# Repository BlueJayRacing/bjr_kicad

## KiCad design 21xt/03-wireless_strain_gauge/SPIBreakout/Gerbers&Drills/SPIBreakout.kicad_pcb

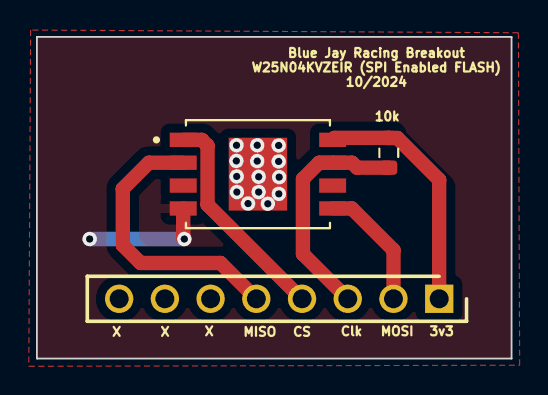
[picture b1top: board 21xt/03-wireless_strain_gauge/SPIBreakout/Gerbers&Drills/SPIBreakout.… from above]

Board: 2 copper layers, 26.4 x 17.9 mm, 3 parts (0 on the bottom side), 5 nets.

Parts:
10k: Rpu; R_0603_1608Metric
F1: SPIFLASH
J1: 61300811821; RHDR8W60P0X254_1X8_2082X250X850P

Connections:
CS: F1.1 (CS#), J1.4
Clk: 10k.2, F1.7 (CLK), J1.3
D0/MISO: F1.2 (DO(IO1)), J1.5
DI/MOSI: F1.5 (DI(IO0)), J1.2
VCC: 10k.1, F1.8 (VCC), J1.1

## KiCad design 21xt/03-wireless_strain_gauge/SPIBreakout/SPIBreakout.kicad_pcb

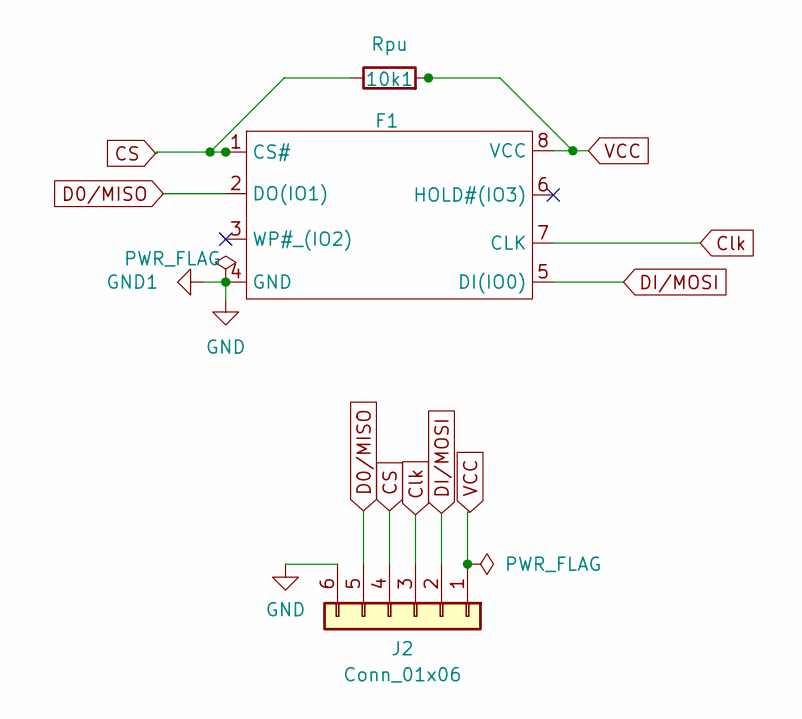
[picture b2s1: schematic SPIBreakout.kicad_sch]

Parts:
10k1: Rpu; R_0603_1608Metric
F1: SPIFLASH
J2: Conn_01x06; PinHeader_1x06_P2.00mm_Vertical

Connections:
CS: 10k1.1, F1.1 (CS#), J2.4
Clk: F1.7 (CLK), J2.3
D0/MISO: F1.2 (DO(IO1)), J2.5
DI/MOSI: F1.5 (DI(IO0)), J2.2
GND: F1.4 (GND), J2.6
VCC: 10k1.2, F1.8 (VCC), J2.1

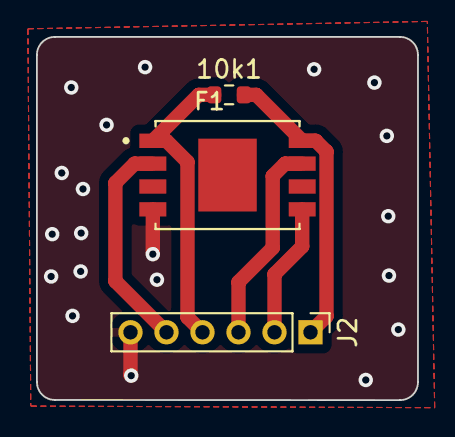
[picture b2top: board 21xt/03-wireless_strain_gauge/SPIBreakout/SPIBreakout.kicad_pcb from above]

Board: 2 copper layers, 21.2 x 20.2 mm, 3 parts (0 on the bottom side), 6 nets.

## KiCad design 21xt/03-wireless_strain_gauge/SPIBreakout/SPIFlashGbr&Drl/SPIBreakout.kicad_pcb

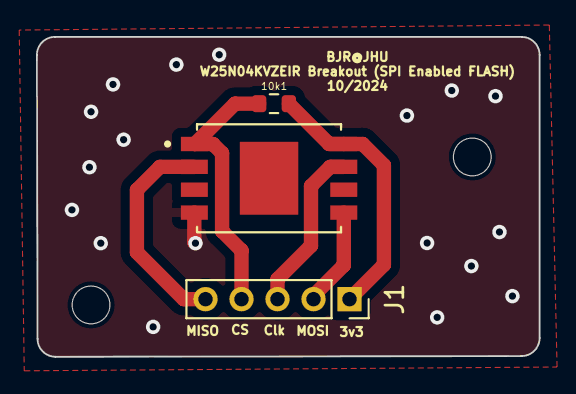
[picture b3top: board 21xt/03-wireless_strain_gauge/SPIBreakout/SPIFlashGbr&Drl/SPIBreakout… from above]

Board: 2 copper layers, 27.9 x 17.8 mm, 3 parts (0 on the bottom side), 5 nets.

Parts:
10k1: Rpu; R_0603_1608Metric
F1: SPIFLASH
J1: Conn_01x05; PinSocket_1x05_P2.00mm_Vertical

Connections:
CS: 10k1.1, F1.1 (CS#), J1.4
Clk: F1.7 (CLK), J1.3
D0/MISO: F1.2 (DO(IO1)), J1.5
DI/MOSI: F1.5 (DI(IO0)), J1.2
VCC: 10k1.2, F1.8 (VCC), J1.1

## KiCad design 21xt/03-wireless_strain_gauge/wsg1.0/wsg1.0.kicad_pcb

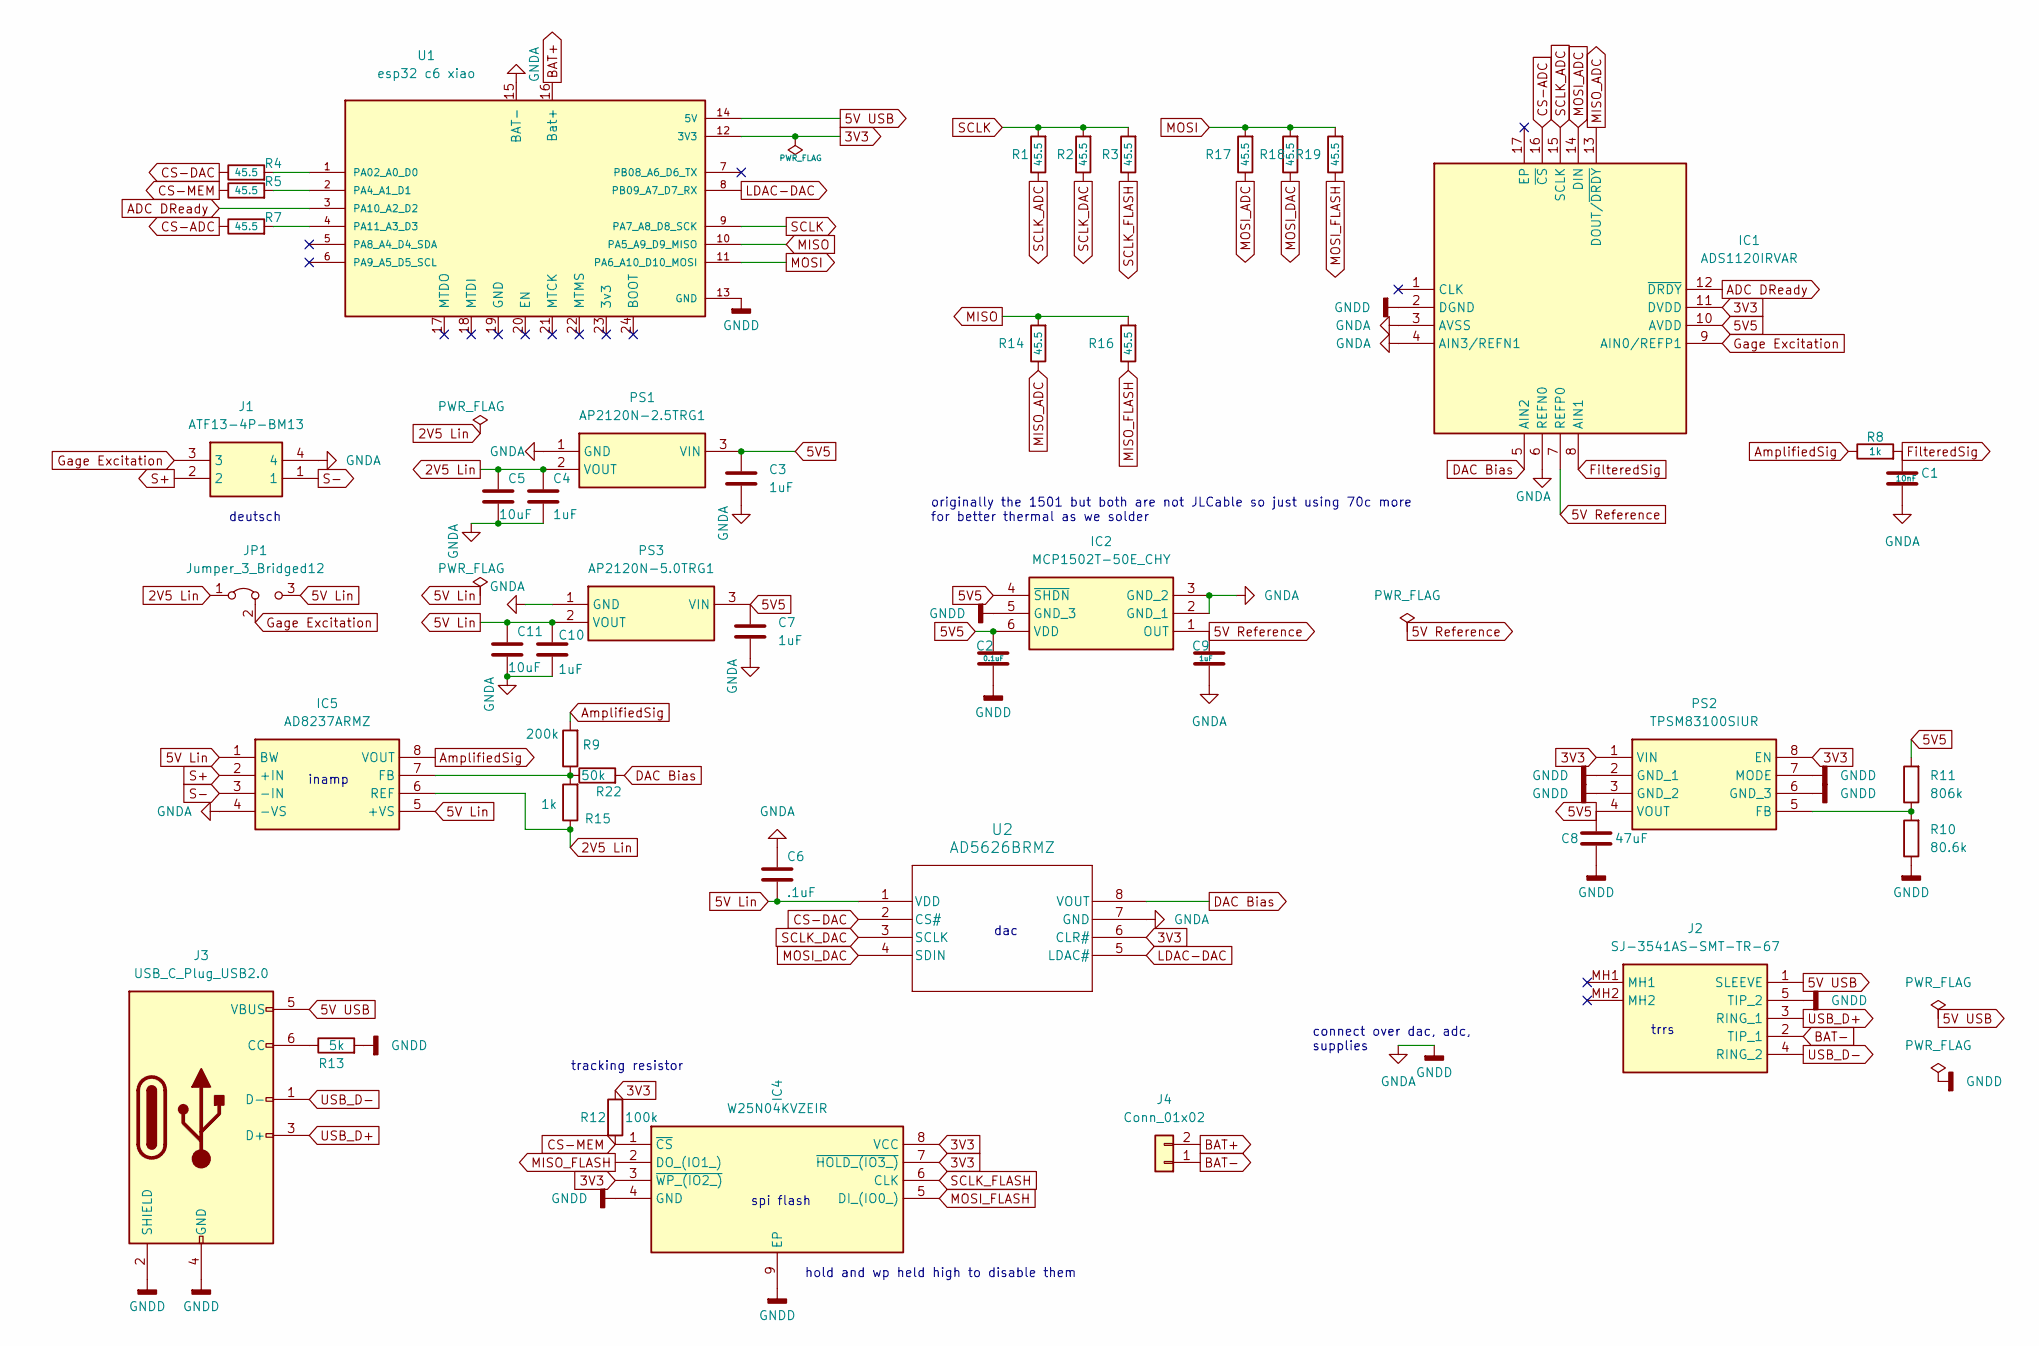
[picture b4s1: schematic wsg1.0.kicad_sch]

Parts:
C1: 10nF; C_0402_1005Metric
C2: 0.1uF; C_0402_1005Metric
C3, C4, C7, C9, C10: 1uF; C_0402_1005Metric
C5, C11: 10uF; C_0402_1005Metric
C6: .1uF; C_0402_1005Metric
C8: 47uF; C_0805_2012Metric
IC1: ADS1120IRVAR; QFN50P350X350X100-17N-D; Mouser Part Number 595-ADS1120IRVAR
IC2: MCP1502T-50E_CHY; SOT95P280X145-6N; Mouser Part Number 579-MCP1501T-50E/CHY
IC4: W25N04KVZEIR; SON127P800X600X80-9N-D; Mouser Part Number 454-W25N04KVZEIR
IC5: AD8237ARMZ; SOP65P490X110-8N; Mouser Part Number 584-AD8237ARMZ
J1: ATF13-4P-BM13; DTF134PG003; Mouser Part Number 571-DTF13-4P-G003
J2: SJ-3541AS-SMT-TR-67; SJ3541ASSMTTR67; Manufacturer_Part_Number SJ-3541AS-SMT-TR-67
J3: USB_C_Plug_USB2.0; USB_C_PLACE
J4: Conn_01x02; JST_PH_S2B-PH-K_1x02_P2.00mm_Horizontal
JP1: Jumper_3_Bridged12; SolderJumper-3_P2.0mm_Open_TrianglePad1.0x1.5mm
PS1: AP2120N-2.5TRG1; Mouser Part Number 621-AP2120N-5.0TRG1
PS2: TPSM83100SIUR; Mouser Part Number 595-TPSM83100SIUR
PS3: AP2120N-5.0TRG1; Mouser Part Number 621-AP2120N-5.0TRG1
R1, R2, R3, R4, R5, R7, R14, R16, R17, R18, R19: 45.5; R_0402_1005Metric
R8, R15: 1k; R_0402_1005Metric
R9: 200k; R_0402_1005Metric
R10: 80.6k; R_0402_1005Metric
R11: 806k; R_0402_1005Metric
R12: 100k; R_0402_1005Metric
R13: 5k; R_0402_1005Metric
R22: 50k; R_0402_1005Metric
U1: esp32 c6 xiao; esp32 c6 smt; PARTREV N/A
U2: AD5626BRMZ; AD5626

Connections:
2V5 Lin: C4.1, C5.1, IC5.6 (REF), JP1.1 (A), PS1.2 (VOUT), R15.1
3V3: IC1.11 (DVDD), IC4.3 (~WP_(IO2_)), IC4.7 (~HOLD_(IO3_)), IC4.8 (VCC), PS2.1 (VIN), PS2.8 (EN), R12.1, U1.12 (3V3), U2.6 (CLR#)
5V5: C2.1, C3.1, C7.1, C8.1, IC1.10 (AVDD), IC2.4 (~SHDN), IC2.6 (VDD), PS1.3 (VIN), PS2.4 (VOUT), PS3.3 (VIN), R11.2
5V Lin: C6.2, C10.1, C11.1, IC5.1 (BW), IC5.5 (+VS), JP1.3 (B), PS3.2 (VOUT), U2.1 (VDD)
5V Reference: C9.1, IC1.7 (REFP0), IC2.1 (OUT)
5V USB: J2.1 (SLEEVE), J3.5 (VBUS), U1.14 (5V)
ADC DReady: IC1.12 (~DRDY), U1.3 (PA10_A2_D2)
AmplifiedSig: IC5.8 (VOUT), R8.1, R9.2
BAT+: J4.2, U1.16 (Bat+)
BAT-: J2.2 (TIP_1), J4.1
CS-ADC: IC1.16 (~CS), R7.1
CS-DAC: R4.1, U2.2 (CS#)
CS-MEM: IC4.1 (~CS), R5.1, R12.2
DAC Bias: IC1.5 (AIN2), R22.2, U2.8 (VOUT)
FilteredSig: C1.1, IC1.8 (AIN1), R8.2
GNDA: C1.2, C2.2, C3.2, C4.2, C5.2, C6.1, C7.2, C8.2, C9.2, C10.2, C11.2, IC1.2 (DGND), IC1.3 (AVSS), IC1.4 (AIN3/REFN1), IC1.6 (REFN0), IC2.2 (GND_1), IC2.3 (GND_2), IC2.5 (GND_3), IC4.4 (GND), IC4.9 (EP), IC5.4 (-VS), J1.4, J2.5 (TIP_2), J3.2 (SHIELD), J3.4 (GND), PS1.1 (GND), PS2.2 (GND_1), PS2.3 (GND_2), PS2.6 (GND_3), PS2.7 (MODE), PS3.1 (GND), R10.1, R13.2, U1.13 (GND), U1.15 (BAT-), U2.7 (GND)
Gage Excitation: IC1.9 (AIN0/REFP1), J1.3, JP1.2 (C)
LDAC-DAC: U1.8 (PB09_A7_D7_RX), U2.5 (LDAC#)
MISO: R14.2, R16.2, U1.10 (PA5_A9_D9_MISO)
MISO_ADC: IC1.13 (DOUT/~DRDY), R14.1
MISO_FLASH: IC4.2 (DO_(IO1_)), R16.1
MOSI: R17.2, R18.2, R19.2, U1.11 (PA6_A10_D10_MOSI)
MOSI_ADC: IC1.14 (DIN), R17.1
MOSI_DAC: R18.1, U2.4 (SDIN)
MOSI_FLASH: IC4.5 (DI_(IO0_)), R19.1
unnamed: IC5.7 (FB), R9.1, R15.2, R22.1
unnamed: J3.6 (CC), R13.1
unnamed: PS2.5 (FB), R10.2, R11.1
unnamed: R4.2, U1.1 (PA02_A0_D0)
unnamed: R5.2, U1.2 (PA4_A1_D1)
unnamed: R7.2, U1.4 (PA11_A3_D3)
S+: IC5.2 (+IN), J1.2
S-: IC5.3 (-IN), J1.1
SCLK: R1.2, R2.2, R3.2, U1.9 (PA7_A8_D8_SCK)
SCLK_ADC: IC1.15 (SCLK), R1.1
SCLK_DAC: R2.1, U2.3 (SCLK)
SCLK_FLASH: IC4.6 (CLK), R3.1
USB_D+: J2.3 (RING_1), J3.3 (D+)
USB_D-: J2.4 (RING_2), J3.1 (D-)

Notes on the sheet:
deutsch
connect over dac, adc, supplies
originally the 1501 but both are not JLCable so just using 70c more for better thermal as we solder
trrs
spi flash
hold and wp held high to disable them
dac
inamp
tracking resistor

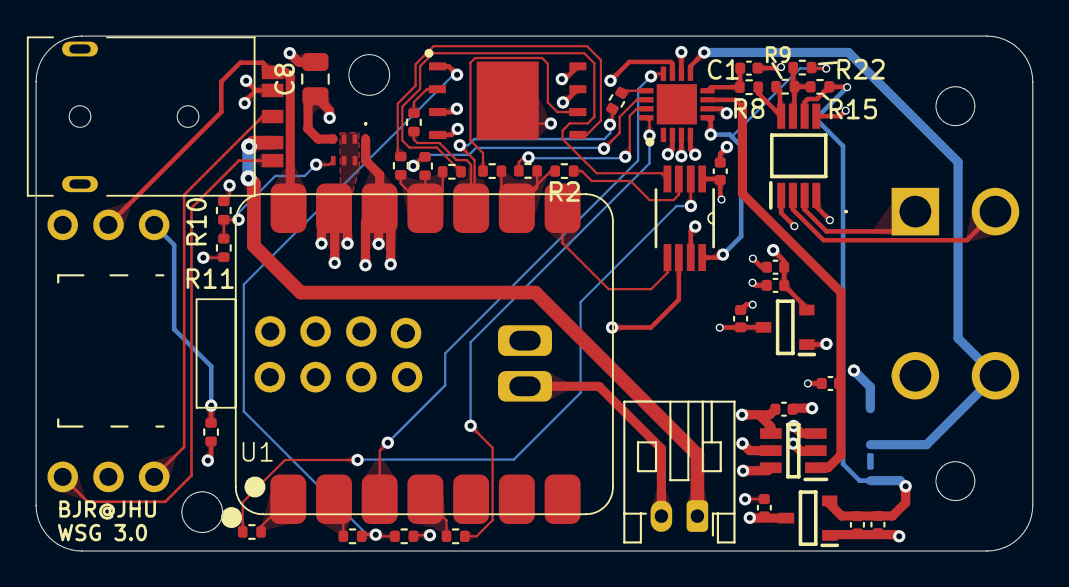
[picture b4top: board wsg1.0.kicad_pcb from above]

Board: 4 copper layers, 55.4 x 28.6 mm, 44 parts (1 on the bottom side), 39 nets.

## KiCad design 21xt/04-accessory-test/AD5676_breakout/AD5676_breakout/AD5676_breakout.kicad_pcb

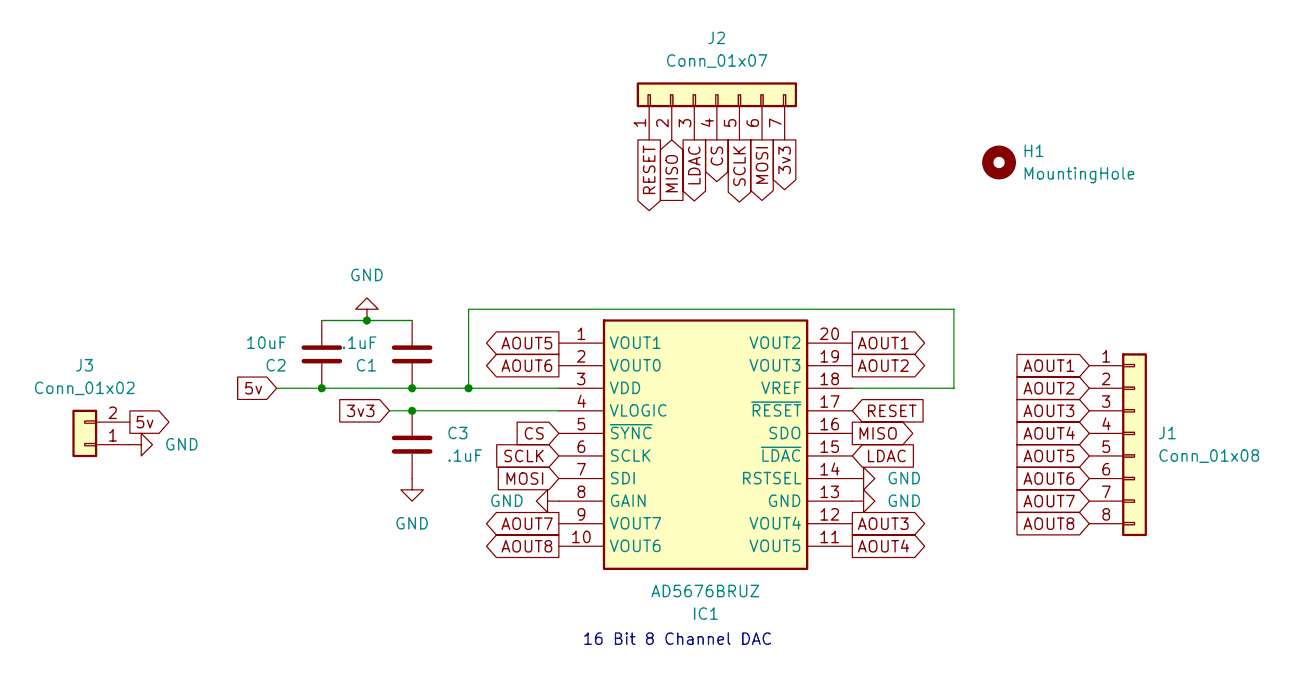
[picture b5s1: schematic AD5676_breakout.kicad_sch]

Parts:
C1, C3: .1uF; C_0603_1608Metric
C2: 10uF; C_0603_1608Metric
H1: MountingHole; MountingHole_2.7mm_M2.5_DIN965_Pad
IC1: AD5676BRUZ; AD5676; Mouser Part Number 584-AD5676BRUZ
J1: Conn_01x08; PinHeader_1x08_P2.54mm_Vertical
J2: Conn_01x07; PinHeader_1x07_P2.54mm_Vertical
J3: Conn_01x02; PinHeader_1x02_P2.54mm_Vertical

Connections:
3v3: C3.1, IC1.4 (VLOGIC), J2.7
5v: C1.1, C2.1, IC1.3 (VDD), IC1.18 (VREF), J3.2
AOUT1: IC1.20 (VOUT2), J1.1
AOUT2: IC1.19 (VOUT3), J1.2
AOUT3: IC1.12 (VOUT4), J1.3
AOUT4: IC1.11 (VOUT5), J1.4
AOUT5: IC1.1 (VOUT1), J1.5
AOUT6: IC1.2 (VOUT0), J1.6
AOUT7: IC1.9 (VOUT7), J1.7
AOUT8: IC1.10 (VOUT6), J1.8
CS: IC1.5 (~SYNC), J2.4
GND: C1.2, C2.2, C3.2, IC1.8 (GAIN), IC1.13 (GND), IC1.14 (RSTSEL), J3.1
LDAC: IC1.15 (~LDAC), J2.3
MISO: IC1.16 (SDO), J2.2
MOSI: IC1.7 (SDI), J2.6
RESET: IC1.17 (~RESET), J2.1
SCLK: IC1.6 (SCLK), J2.5

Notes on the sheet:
16 Bit 8 Channel DAC

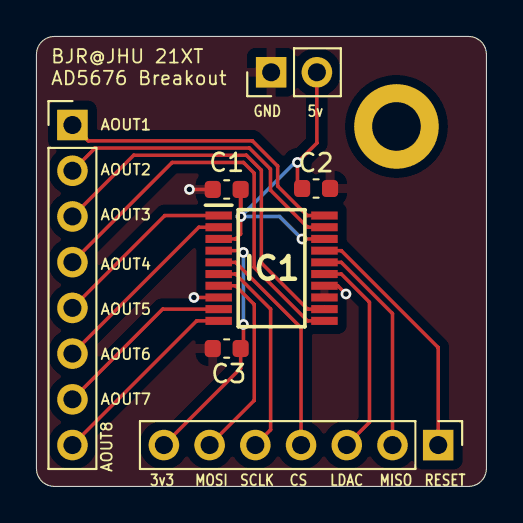
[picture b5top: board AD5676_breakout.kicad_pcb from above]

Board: 2 copper layers, 25.0 x 25.0 mm, 8 parts (0 on the bottom side), 17 nets.

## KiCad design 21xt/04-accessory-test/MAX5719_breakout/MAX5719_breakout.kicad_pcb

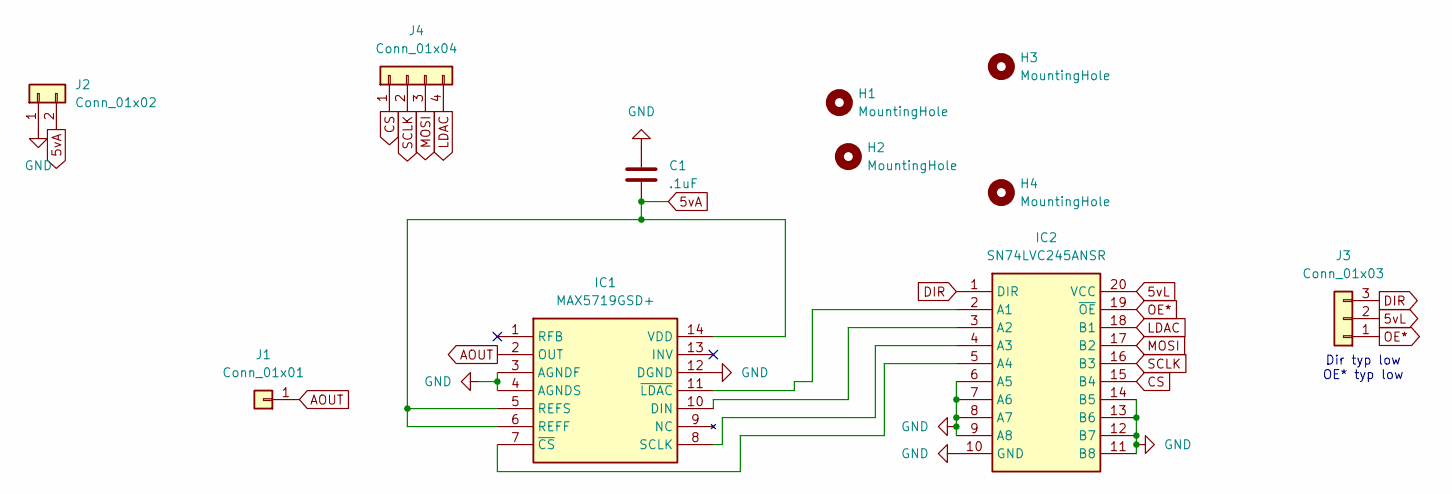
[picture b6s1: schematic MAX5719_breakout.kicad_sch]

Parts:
C1: .1uF; C_0603_1608Metric
H1, H2, H3, H4: MountingHole; MountingHole_2.7mm_M2.5_DIN965
IC1: MAX5719GSD+; MAX5719; Mouser Part Number 700-MAX5719GSD+
IC2: SN74LVC245ANSR; SOIC127P780X200-20N; Mouser Part Number 595-SN74LVC245ANSR
J1: Conn_01x01; PinHeader_1x01_P2.54mm_Vertical
J2: Conn_01x02; PinHeader_1x02_P2.54mm_Vertical
J3: Conn_01x03; PinHeader_1x03_P2.54mm_Vertical
J4: Conn_01x04; PinHeader_1x04_P2.54mm_Vertical

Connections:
5vA: C1.2, IC1.5 (REFS), IC1.6 (REFF), IC1.14 (VDD), J2.2
5vL: IC2.20 (VCC), J3.2
AOUT: IC1.2 (OUT), J1.1
CS: IC2.15 (B4), J4.1
DIR: IC2.1 (DIR), J3.3
GND: C1.1, IC1.3 (AGNDF), IC1.4 (AGNDS), IC1.12 (DGND), IC2.6 (A5), IC2.7 (A6), IC2.8 (A7), IC2.9 (A8), IC2.10 (GND), IC2.11 (B8), IC2.12 (B7), IC2.13 (B6), IC2.14 (B5), J2.1
LDAC: IC2.18 (B1), J4.4
MOSI: IC2.17 (B2), J4.3
unnamed: IC1.10 (DIN), IC2.3 (A2)
unnamed: IC1.8 (SCLK), IC2.4 (A3)
unnamed: IC1.7 (~CS), IC2.5 (A4)
unnamed: IC1.11 (~LDAC), IC2.2 (A1)
OE*: IC2.19 (~OE), J3.1
SCLK: IC2.16 (B3), J4.2

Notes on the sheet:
Dir typ low OE* typ low

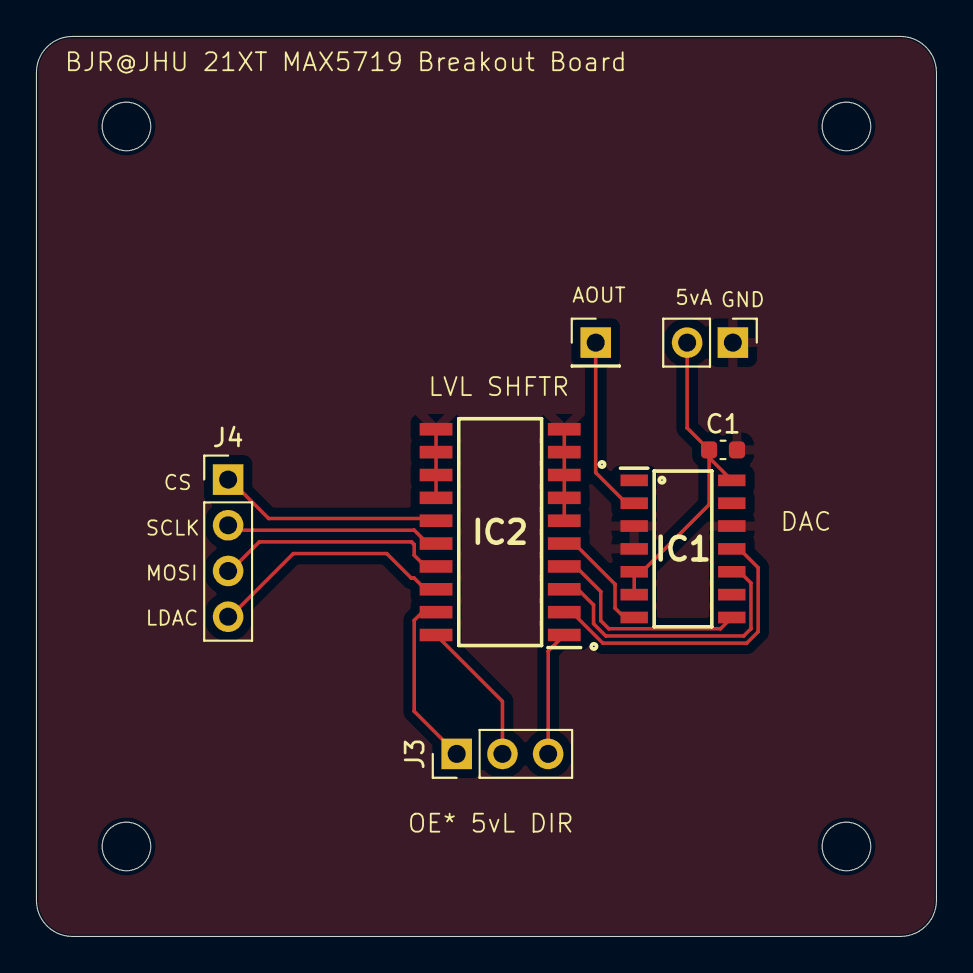
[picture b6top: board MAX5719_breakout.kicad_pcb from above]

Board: 2 copper layers, 50.0 x 50.0 mm, 11 parts (0 on the bottom side), 14 nets.

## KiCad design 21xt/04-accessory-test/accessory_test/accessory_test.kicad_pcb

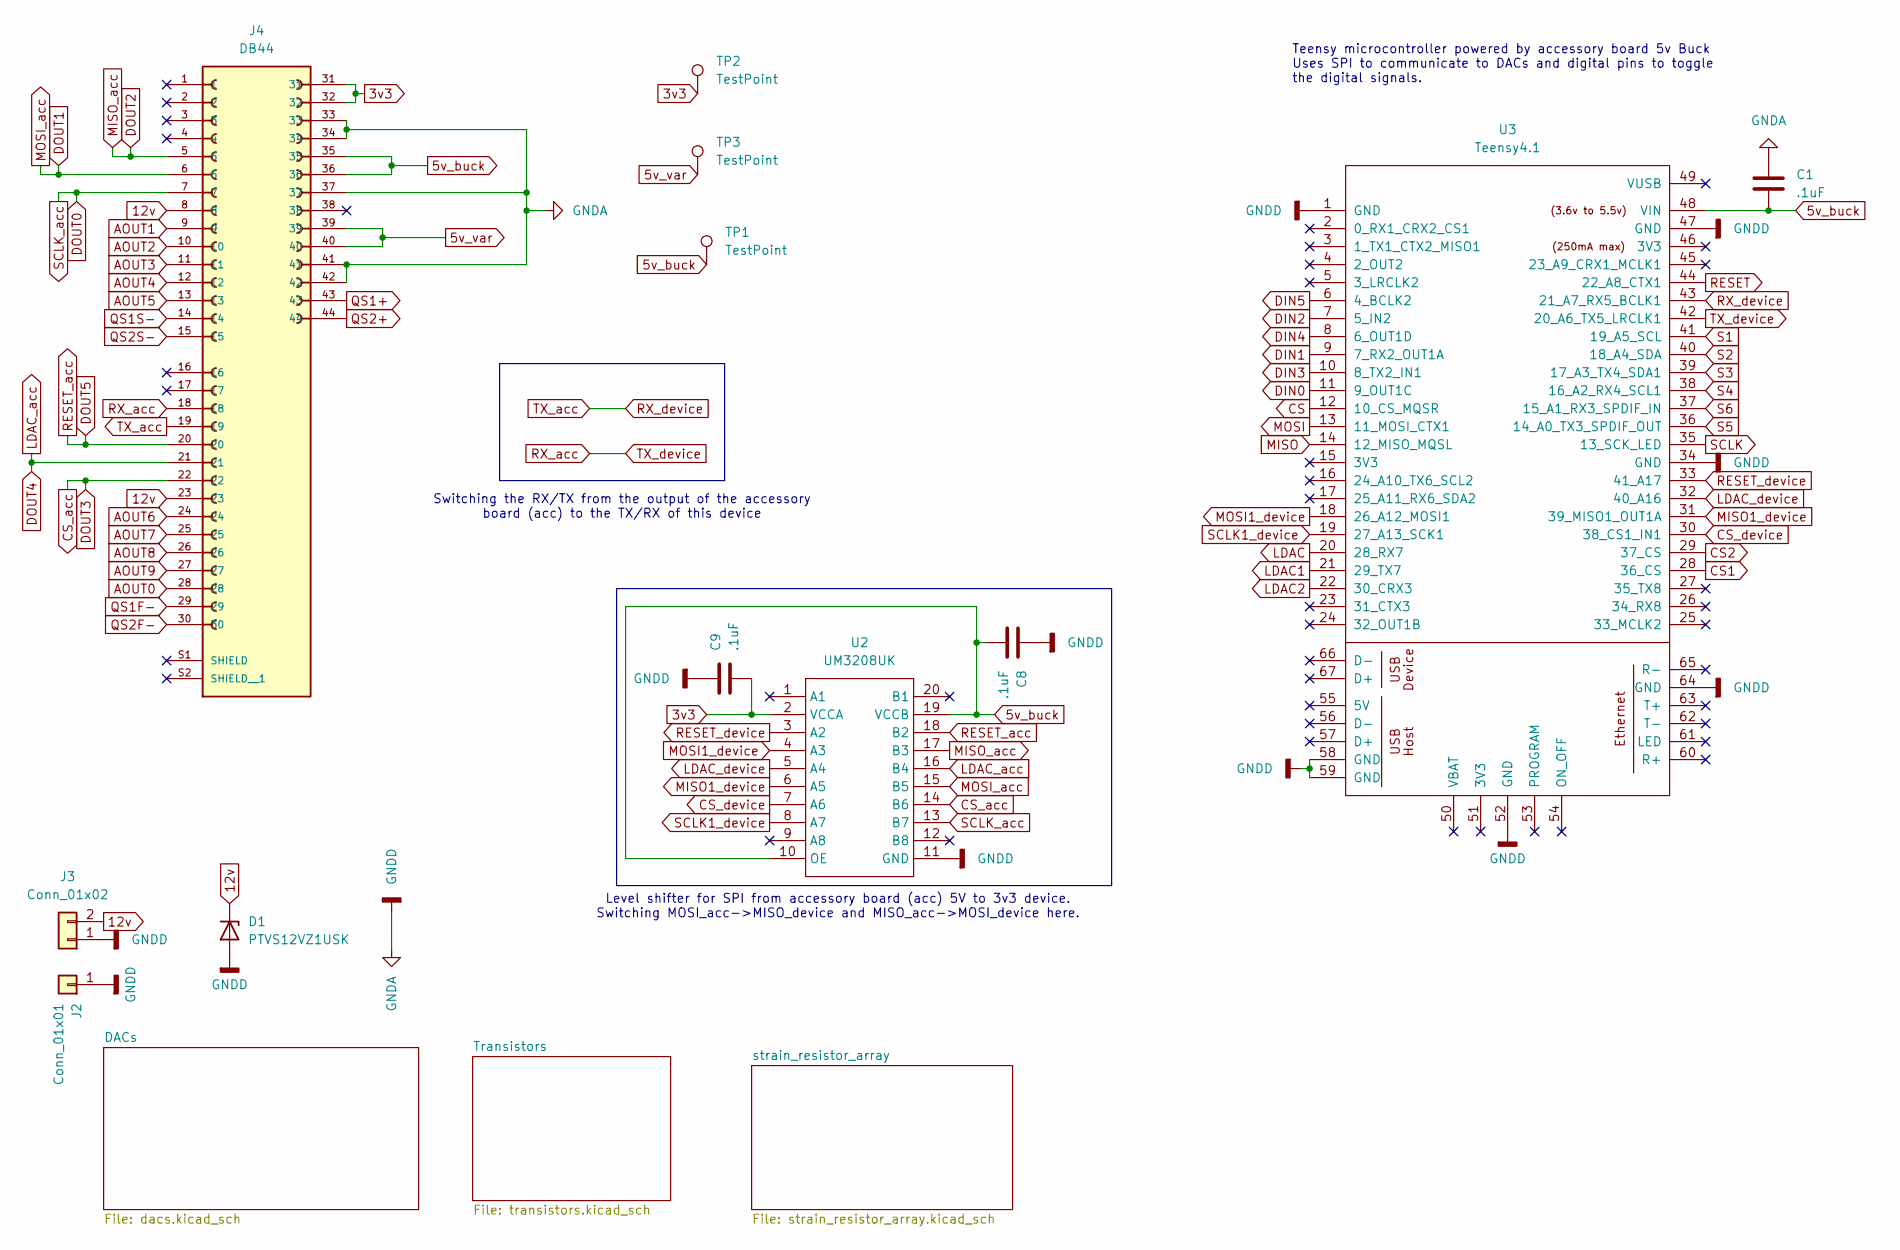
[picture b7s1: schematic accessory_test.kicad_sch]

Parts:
C1, C8, C9: .1uF; C_0603_1608Metric
D1: PTVS12VZ1USK; C_0603_1608Metric
J2: Conn_01x01; PinHeader_1x01_P2.54mm_Vertical
J3: Conn_01x02; PinHeader_1x02_P2.54mm_Vertical
J4: DB44; PARTREV C
TP1, TP2, TP3: TestPoint; TestPoint_Pad_2.0x2.0mm
U2: UM3208UK; TSSOP-20_4.4x6.5mm_P0.65mm
U3: Teensy4.1; Teensy41

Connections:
3v3: C9.2, J4.31, J4.32, TP2.1, U2.2 (VCCA); also elsewhere on the board
5v_buck: C1.2, C8.2, J4.35, J4.36, TP1.1, U2.10 (OE), U2.19 (VCCB), U3.48 (VIN); also elsewhere on the board
5v_var: J4.39, J4.40, TP3.1; also elsewhere on the board
12v: D1.1 (K), J3.2, J4.8, J4.23
AOUT0: J4.28; also elsewhere on the board
AOUT1: J4.9; also elsewhere on the board
AOUT2: J4.10; also elsewhere on the board
AOUT3: J4.11; also elsewhere on the board
AOUT4: J4.12; also elsewhere on the board
AOUT5: J4.13; also elsewhere on the board
AOUT6: J4.24; also elsewhere on the board
AOUT7: J4.25; also elsewhere on the board
AOUT8: J4.26; also elsewhere on the board
AOUT9: J4.27; also elsewhere on the board
CS: U3.12 (10_CS_MQSR); also elsewhere on the board
CS1: U3.28 (36_CS); also elsewhere on the board
CS2: U3.29 (37_CS); also elsewhere on the board
CS_acc: J4.22, U2.14 (B6); also elsewhere on the board
CS_device: U2.7 (A6), U3.30 (38_CS1_IN1)
DIN0: U3.11 (9_OUT1C); also elsewhere on the board
DIN1: U3.9 (7_RX2_OUT1A); also elsewhere on the board
DIN2: U3.7 (5_IN2); also elsewhere on the board
DIN3: U3.10 (8_TX2_IN1); also elsewhere on the board
DIN4: U3.8 (6_OUT1D); also elsewhere on the board
DIN5: U3.6 (4_BCLK2); also elsewhere on the board
DOUT0: J4.7, U2.13 (B7); also elsewhere on the board
DOUT1: J4.6, U2.15 (B5); also elsewhere on the board
DOUT2: J4.5, U2.17 (B3); also elsewhere on the board
DOUT4: J4.21, U2.16 (B4); also elsewhere on the board
DOUT5: J4.20, U2.18 (B2); also elsewhere on the board
GNDA: C1.1, C8.1, C9.1, D1.2 (A), J2.1, J3.1, J4.33, J4.34, J4.37, J4.41, J4.42, U2.11 (GND), U3.1 (GND), U3.34 (GND), U3.47 (GND), U3.52 (GND), U3.58 (GND), U3.59 (GND), U3.64 (GND); also elsewhere on the board
LDAC: U3.20 (28_RX7); also elsewhere on the board
LDAC1: U3.21 (29_TX7); also elsewhere on the board
LDAC2: U3.22 (30_CRX3); also elsewhere on the board
LDAC_device: U2.5 (A4), U3.32 (40_A16)
MISO: U3.14 (12_MISO_MQSL); also elsewhere on the board
MISO1_device: U2.6 (A5), U3.31 (39_MISO1_OUT1A)
MOSI: U3.13 (11_MOSI_CTX1); also elsewhere on the board
MOSI1_device: U2.4 (A3), U3.18 (26_A12_MOSI1)
QS1+: J4.43, J4.44; also elsewhere on the board
QS1F-: J4.14, J4.15, J4.29, J4.30; also elsewhere on the board
RESET: U3.44 (22_A8_CTX1); also elsewhere on the board
RESET_device: U2.3 (A2), U3.33 (41_A17)
RX_acc: J4.18, U3.42 (20_A6_TX5_LRCLK1)
RX_device: J4.19, U3.43 (21_A7_RX5_BCLK1)
S1: U3.41 (19_A5_SCL); also elsewhere on the board
S2: U3.40 (18_A4_SDA); also elsewhere on the board
S3: U3.39 (17_A3_TX4_SDA1); also elsewhere on the board
S4: U3.38 (16_A2_RX4_SCL1); also elsewhere on the board
S5: U3.36 (14_A0_TX3_SPDIF_OUT); also elsewhere on the board
S6: U3.37 (15_A1_RX3_SPDIF_IN); also elsewhere on the board
SCLK: U3.35 (13_SCK_LED); also elsewhere on the board
SCLK1_device: U2.8 (A7), U3.19 (27_A13_SCK1)

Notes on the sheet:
Switching the RX/TX from the output of the accessory board (acc) to the TX/RX of this device
Level shifter for SPI from accessory board (acc) 5V to 3v3 device. Switching MOSI_acc->MISO_device and MISO_acc->MOSI_device here.
Teensy microcontroller powered by accessory board 5v Buck Uses SPI to communicate to DACs and digital pins to toggle the digital signals.

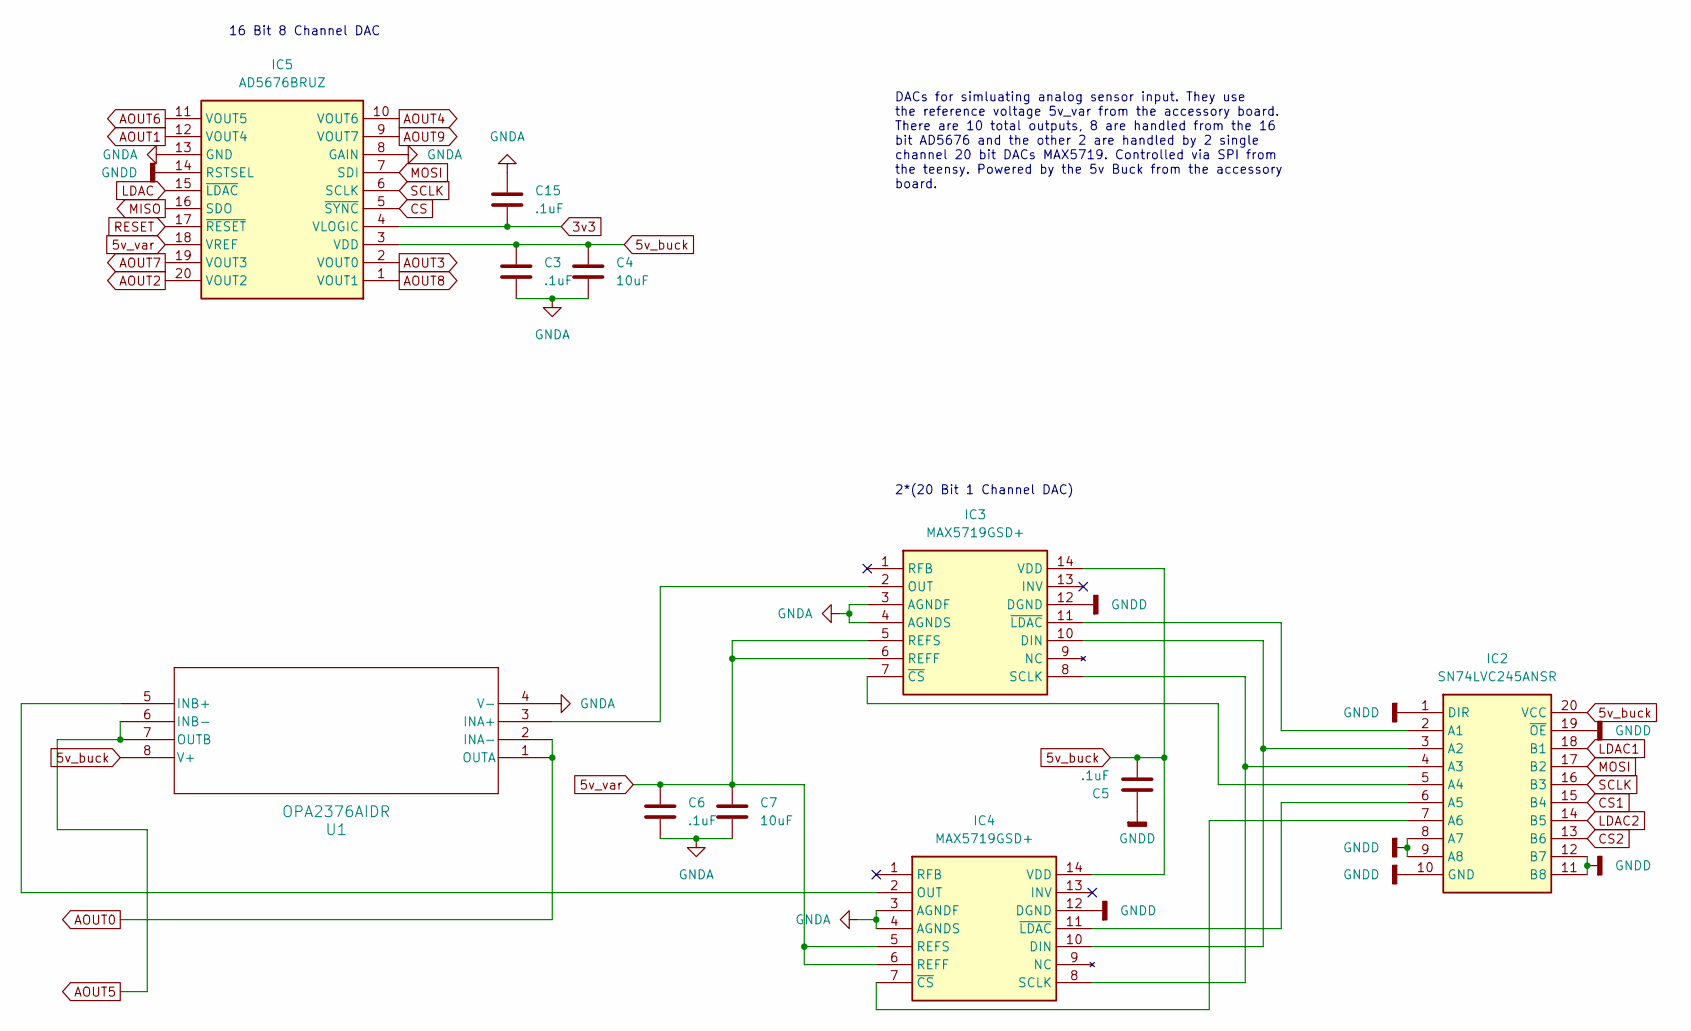
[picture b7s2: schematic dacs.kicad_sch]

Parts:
C3, C5, C6, C15: .1uF; C_0603_1608Metric
C4, C7: 10uF; C_0603_1608Metric
IC2: SN74LVC245ANSR; Mouser Part Number 595-SN74LVC245ANSR
IC3, IC4: MAX5719GSD+; MAX5719; Mouser Part Number 700-MAX5719GSD+
IC5: AD5676BRUZ; AD5676; Mouser Part Number 584-AD5676BRUZ
U1: OPA2376AIDR

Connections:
3v3: C15.2, IC5.4 (VLOGIC); also elsewhere on the board
5v_buck: C3.1, C4.1, C5.2, IC2.20 (VCC), IC3.14 (VDD), IC4.14 (VDD), IC5.3 (VDD), U1.8 (V+); also elsewhere on the board
5v_var: C6.1, C7.1, IC3.5 (REFS), IC3.6 (REFF), IC4.5 (REFS), IC4.6 (REFF), IC5.18 (VREF); also elsewhere on the board
AOUT0: U1.1 (OUTA), U1.2 (INA-); also elsewhere on the board
AOUT1: IC5.12 (VOUT4); also elsewhere on the board
AOUT2: IC5.20 (VOUT2); also elsewhere on the board
AOUT3: IC5.2 (VOUT0); also elsewhere on the board
AOUT4: IC5.10 (VOUT6); also elsewhere on the board
AOUT5: U1.6 (INB-), U1.7 (OUTB); also elsewhere on the board
AOUT6: IC5.11 (VOUT5); also elsewhere on the board
AOUT7: IC5.19 (VOUT3); also elsewhere on the board
AOUT8: IC5.1 (VOUT1); also elsewhere on the board
AOUT9: IC5.9 (VOUT7); also elsewhere on the board
CS: IC5.5 (~SYNC); also elsewhere on the board
CS1: IC2.15 (B4); also elsewhere on the board
CS2: IC2.13 (B6); also elsewhere on the board
GNDA: C3.2, C4.2, C5.1, C6.2, C7.2, C15.1, IC2.1 (DIR), IC2.8 (A7), IC2.9 (A8), IC2.10 (GND), IC2.11 (B8), IC2.12 (B7), IC2.19 (~OE), IC3.3 (AGNDF), IC3.4 (AGNDS), IC3.12 (DGND), IC4.3 (AGNDF), IC4.4 (AGNDS), IC4.12 (DGND), IC5.8 (GAIN), IC5.13 (GND), IC5.14 (RSTSEL), U1.4 (V-); also elsewhere on the board
LDAC: IC5.15 (~LDAC); also elsewhere on the board
LDAC1: IC2.18 (B1); also elsewhere on the board
LDAC2: IC2.14 (B5); also elsewhere on the board
MISO: IC5.16 (SDO); also elsewhere on the board
MOSI: IC2.17 (B2), IC5.7 (SDI); also elsewhere on the board
unnamed: IC2.2 (A1), IC3.11 (~LDAC)
unnamed: IC2.3 (A2), IC3.10 (DIN), IC4.10 (DIN)
unnamed: IC2.4 (A3), IC3.8 (SCLK), IC4.8 (SCLK)
unnamed: IC2.5 (A4), IC3.7 (~CS)
unnamed: IC2.6 (A5), IC4.11 (~LDAC)
unnamed: IC2.7 (A6), IC4.7 (~CS)
unnamed: IC3.2 (OUT), U1.3 (INA+)
unnamed: IC4.2 (OUT), U1.5 (INB+)
RESET: IC5.17 (~RESET); also elsewhere on the board
SCLK: IC2.16 (B3), IC5.6 (SCLK); also elsewhere on the board

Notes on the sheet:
16 Bit 8 Channel DAC
2*(20 Bit 1 Channel DAC)
DACs for simluating analog sensor input. They use the reference voltage 5v_var from the accessory board. There are 10 total outputs, 8 are handled from the 16 bit AD5676 and the other 2 are handled by 2 single channel 20 bit DACs MAX5719. Controlled via SPI from the teensy. Powered by the 5v Buck f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
